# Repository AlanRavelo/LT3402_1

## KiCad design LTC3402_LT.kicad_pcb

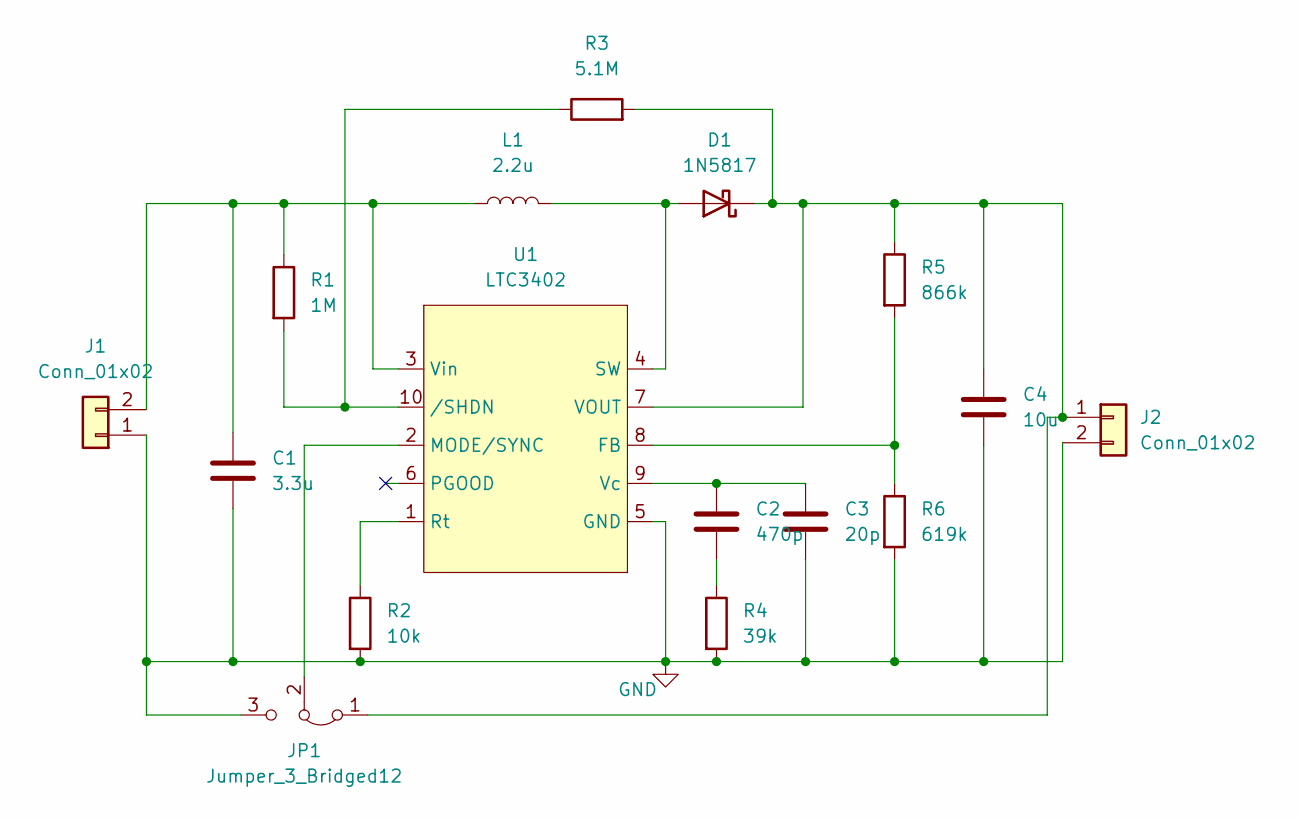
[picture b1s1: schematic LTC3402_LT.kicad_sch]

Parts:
C1: 3.3u; C_Disc_D4.3mm_W1.9mm_P5.00mm
C2: 470p; C_Disc_D4.3mm_W1.9mm_P5.00mm
C3: 20p; C_Disc_D4.3mm_W1.9mm_P5.00mm
C4: 10u; C_Disc_D4.3mm_W1.9mm_P5.00mm
D1: 1N5817; D_DO-41_SOD81_P10.16mm_Horizontal
J1, J2: Conn_01x02; TerminalBlock_Phoenix_MKDS-1,5-2-5.08_1x02_P5.08mm_Horizont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
JP1: Jumper_3_Bridged12; SolderJumper-3_P1.3mm_Open_RoundedPad1.0x1.5mm
L1: 2.2u; L_Axial_L5.3mm_D2.2mm_P7.62mm_Horizontal_Vishay_IM-1
R1: 1M; R_Axial_DIN0207_L6.3mm_D2.5mm_P7.62mm_Horizontal
R2: 10k; R_Axial_DIN0207_L6.3mm_D2.5mm_P7.62mm_Horizontal
R3: 5.1M; R_Axial_DIN0207_L6.3mm_D2.5mm_P7.62mm_Horizontal
R4: 39k; R_Axial_DIN0207_L6.3mm_D2.5mm_P7.62mm_Horizontal
R5: 866k; R_Axial_DIN0207_L6.3mm_D2.5mm_P7.62mm_Horizontal
R6: 619k; R_Axial_DIN0207_L6.3mm_D2.5mm_P7.62mm_Horizontal
U1: LTC3402; DIP-10_W7.62mm_Socket_LongPads

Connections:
GND: C1.2, C3.2, C4.2, J1.1, J2.2, JP1.3 (B), R2.2, R4.2, R6.2, U1.5 (GND)
unnamed: C1.1, J1.2, L1.1, R1.1, U1.3 (Vin)
unnamed: C2.1, C3.1, U1.9 (Vc)
unnamed: C2.2, R4.1
unnamed: C4.1, D1.1 (K), J2.1, JP1.1 (A), R3.2, R5.1, U1.7 (VOUT)
unnamed: D1.2 (A), L1.2, U1.4 (SW)
unnamed: JP1.2 (C), U1.2 (MODE/SYNC)
unnamed: R1.2, R3.1, U1.10 (/SHDN)
unnamed: R2.1, U1.1 (Rt)
unnamed: R5.2, R6.1, U1.8 (FB)

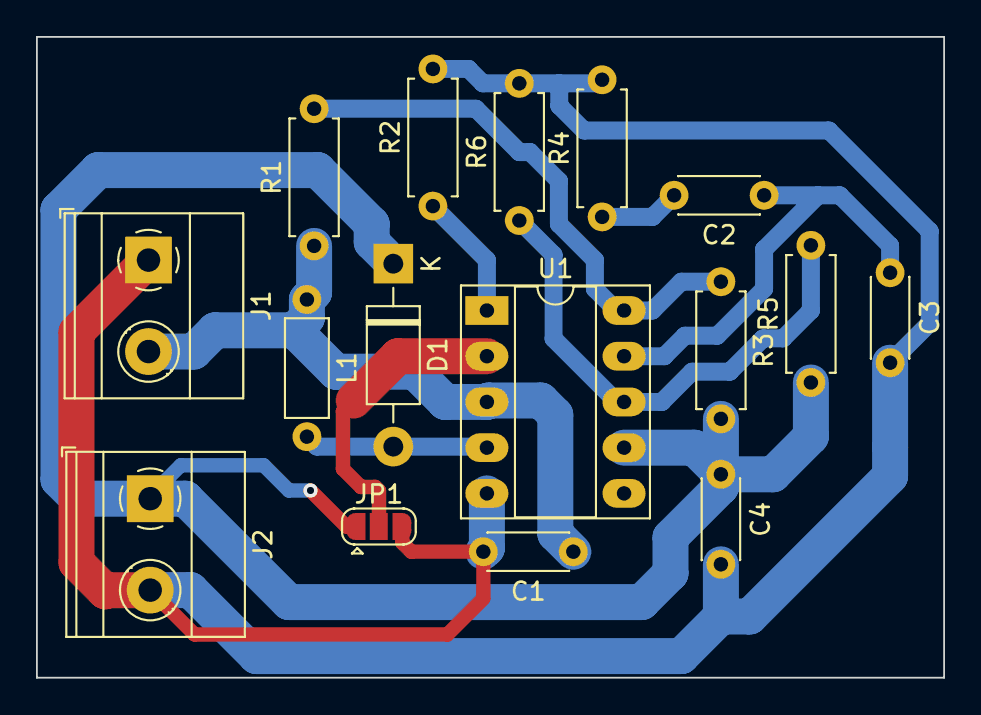
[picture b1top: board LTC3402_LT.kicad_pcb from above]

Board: 2 copper layers, 50.4 x 35.6 mm, 16 parts (0 on the bottom side), 10 nets.
